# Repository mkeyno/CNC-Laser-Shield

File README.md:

# ESP32 CNC Shield  with HMI
ESP32 is one the greatest MCU when need robots wifi communication, 

this double core MCU has a great feature when concise Datalink and processing Data is needed, one core for handling the HMI interface and other core for data delivery to G-Code interpreter  board 

following is the  HMI interface for the CNC operator 
G-code can be directly uploaded on the webpage buffer and fed to the CNC bus line

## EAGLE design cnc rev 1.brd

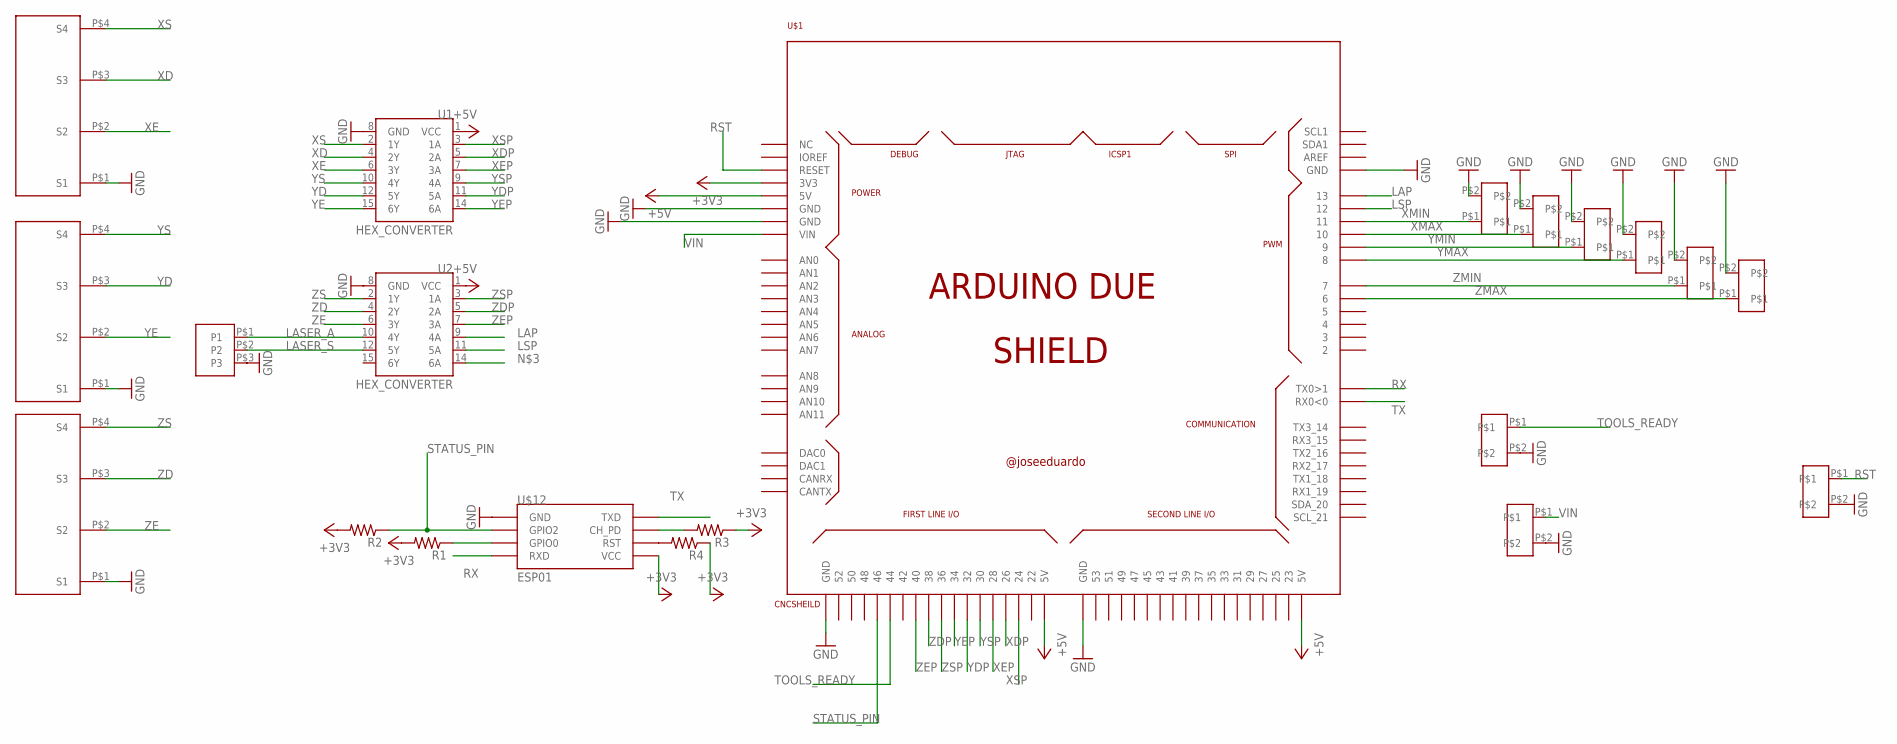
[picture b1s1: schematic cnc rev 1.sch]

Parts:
INPUT, INPUT1: PIN_LOCK_1X2; PIN_LOCK1X2
R1, R2, R3, R4: 0.1OHM-1/2W-1%(1210); 1210
U1, U2: HEX_CONVERTER; SO016
U$1: CNCSHEILD
U$2, U$3, U$4: TBC1X4; PTC1X4
U$5, U$6, U$7, U$8, U$9, U$10, U$11: PIN_LOCK_1X2; PIN_LOCK1X2
U$12: ESP01
U$13: PIN_LOCK_1X3; PIN_LOCK1X3

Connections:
+3V3: R1.2, R2.2, R3.1, R4.1, U$1.3V3, U$12.VCC
+5V: U1.1 (VCC), U2.1 (VCC), U$1.5V0 (5V), U$1.5V0_1 (5V), U$1.5V0_2 (5V)
GND: INPUT.P$2, INPUT1.P$2, U$1.GND, U$1.GND_1 (GND), U$1.GND_2 (GND), U$1.GND_3 (GND), U$1.GND_4 (GND), U$2.P$1 (S1), U$3.P$1 (S1), U$4.P$1 (S1), U$5.P$2, U$6.P$2, U$7.P$2, U$8.P$2, U$9.P$2, U$10.P$2, U$11.P$2
LAP: U2.9 (4A), U$1.13
LASER_A: U2.10 (4Y), U$13.P$1 (P1)
LASER_S: U2.12 (5Y), U$13.P$2 (P2)
LSP: U2.11 (5A), U$1.12
unnamed: R1.1, U$12.GPIO0
unnamed: R3.2, U$12.CH_PD
unnamed: R4.2, U$12.RST
RST: U$1.RESET, U$11.P$1
RX: U$1.1 (TX0>1), U$12.RX (RXD)
STATUS_PIN: R2.1, U$1.46, U$12.GPIO2
TOOLS_READY: INPUT1.P$1, U$1.44
TX: U$1.0 (RX0<0), U$12.TX (TXD)
VIN: INPUT.P$1, U$1.VIN
XD: U1.4 (2Y), U$4.P$3 (S3)
XDP: U1.5 (2A), U$1.26
XE: U1.6 (3Y), U$4.P$2 (S2)
XEP: U1.7 (3A), U$1.28
XMAX: U$1.10, U$8.P$1
XMIN: U$1.11, U$5.P$1
XS: U1.2 (1Y), U$4.P$4 (S4)
XSP: U1.3 (1A), U$1.24
YD: U1.12 (5Y), U$2.P$3 (S3)
YDP: U1.11 (5A), U$1.32
YE: U1.15 (6Y), U$2.P$2 (S2)
YEP: U1.14 (6A), U$1.34
YMAX: U$1.8, U$9.P$1
YMIN: U$1.9, U$6.P$1
YS: U1.10 (4Y), U$2.P$4 (S4)
YSP: U1.9 (4A), U$1.30
ZD: U2.4 (2Y), U$3.P$3 (S3)
ZDP: U2.5 (2A), U$1.38
ZE: U2.6 (3Y), U$3.P$2 (S2)
ZEP: U2.7 (3A), U$1.40
ZMAX: U$1.6, U$10.P$1
ZMIN: U$1.7, U$7.P$1
ZS: U2.2 (1Y), U$3.P$4 (S4)
ZSP: U2.3 (1A), U$1.36

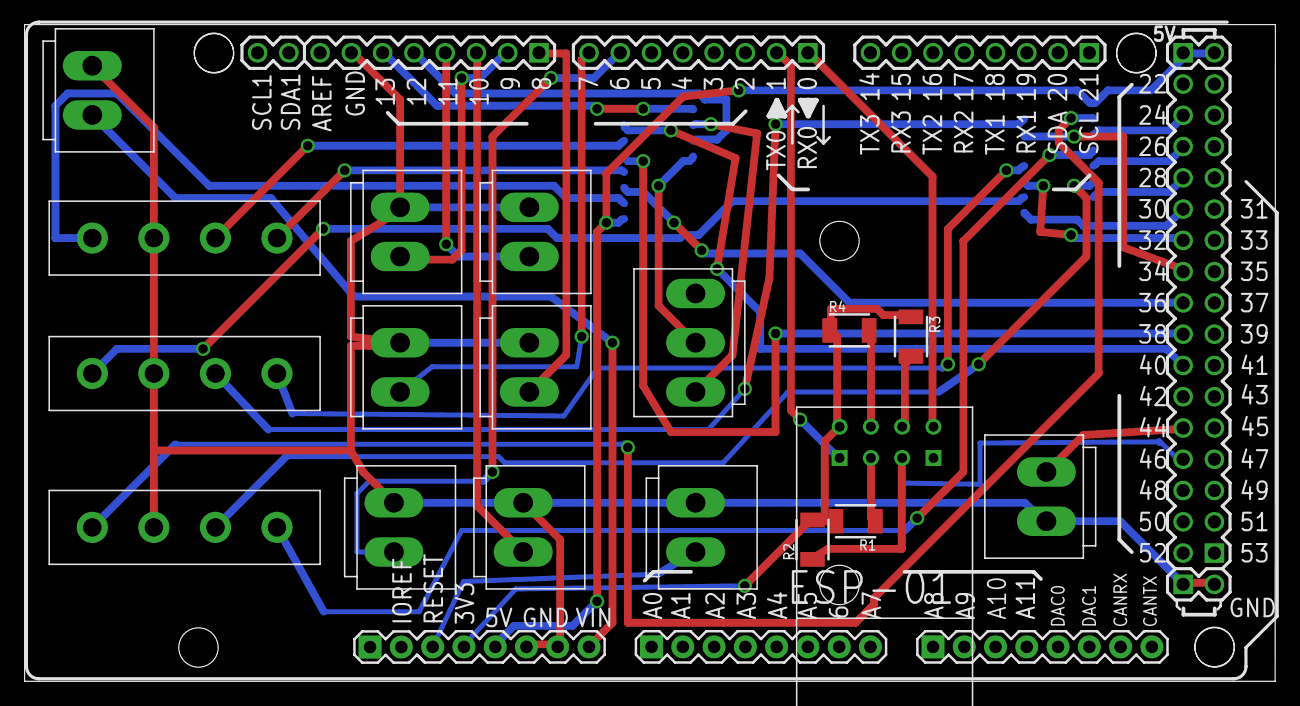
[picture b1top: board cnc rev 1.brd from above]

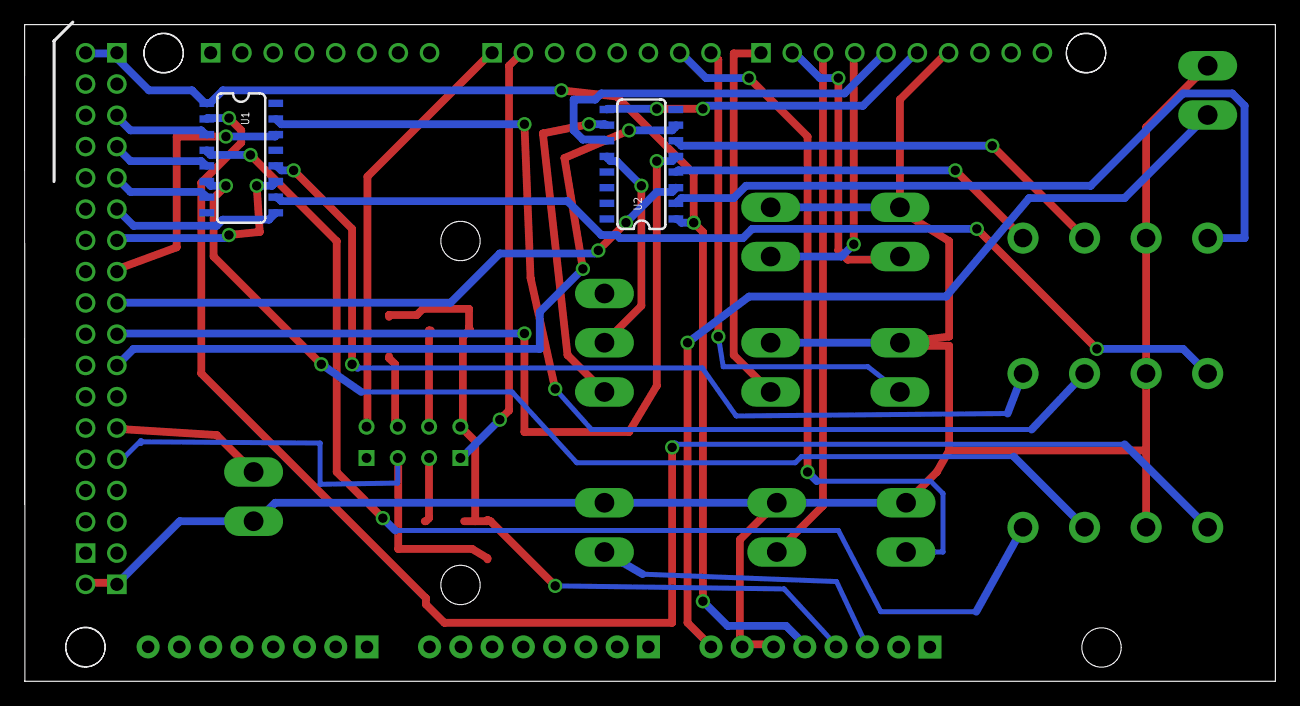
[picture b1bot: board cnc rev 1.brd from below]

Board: 2 copper layers, 101.6 x 53.3 mm, 21 parts (2 on the bottom side), 40 nets.

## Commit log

2016-03-09 Added files via upload

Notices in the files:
parts and their libraries:
SparkFun-DigitalIC: Licensing: Creative Commons ShareAlike 4.0 International - https://creativecommons.org/licenses/by-sa/4.0
